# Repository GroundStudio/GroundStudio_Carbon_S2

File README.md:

GroundStudio Carbon S2
====================================

Get it from [ardushop.ro](https://ardushop.ro/en/groundstudio/1814-placa-de-dezvoltare-carbon-s2-6427854000415.html#product-comments-list-header)

Explore all the GroundStudio products at [ardushop.ro](https://ardushop.ro/en/37-groundstudio)

Description
-------------------
Features highly integrated ESP32-S2 with 2.4 GHz WiFi, 4MB Flash, 320kB SRAM, 128kB ROM, 18 GPIO, 10 ADC, 8 touch sensitive pins, 2 UART, I²C 3V3 adapter, RGB smart LED and 1 cell LiPo/LiIon battery charger with optional battery connector.

Contents
-------------------

* [/Documentation](https://github.com/GroundStudio/GroundStudio_Carbon_S2/tree/main/Documentation) -- Pinout.
* [/Hardware](https://github.com/GroundStudio/GroundStudio_Carbon_S2/tree/main/Hardware) -- Schematics, layout.

Versions
-------------------
*(Not all tags shown)*

* [REV0.0.2]
  * changed GPIO3 with GPIO12 between R3 and R8 because GPIO12 cannot be pulled high while in flash mode
  * added 100nF in parallel with R7 for better battery voltage level reading
  * modified the i2c connector label for better visibility
  * adjusted the position of the solder-jumper labels
  * increased the copper fill area under the uC for better cooling

License
-------------------

This is released under the [Attribution-ShareAlike 4.0 International (CC BY-SA 4.0)](https://creativecommons.org/licenses/by-sa/4.0/) license. 
**You are welcome to use this for commercial purposes.**

Please consider contributing back to this project or others to help the open-source hardware community continue to thrive and grow! 

Certifications:

[Open Source Hardware Association](https://certification.oshwa.org/ro000008.html)   
   
[
](https://certification.oshwa.org/ro000008.html)

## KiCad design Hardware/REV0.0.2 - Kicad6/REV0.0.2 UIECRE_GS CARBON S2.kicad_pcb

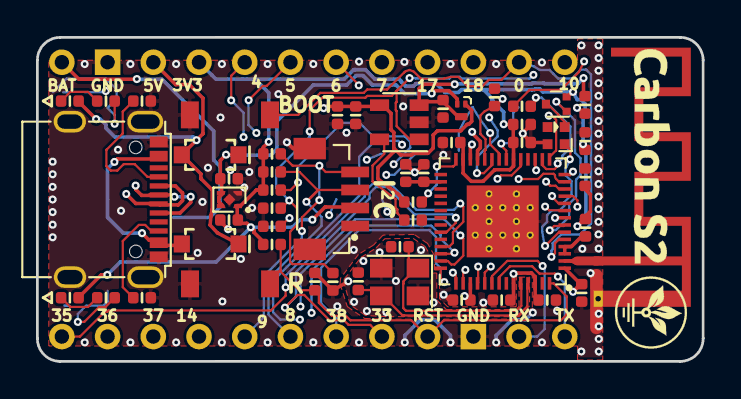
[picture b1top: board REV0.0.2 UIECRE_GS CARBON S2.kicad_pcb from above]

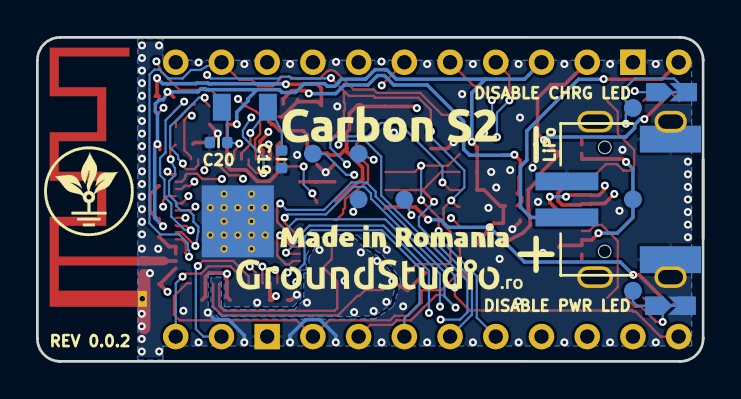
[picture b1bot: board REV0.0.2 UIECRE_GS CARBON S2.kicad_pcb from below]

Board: 4 copper layers, 37.0 x 18.0 mm, 67 parts (8 on the bottom side), 52 nets.

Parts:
A1: SWRA117D_2.4GHz; Texas_SWRA117D_2.4GHz_Left
C1, C4, C8, C9, C11, C14, C15: C_0402_1uF_10V; C_0402_alt
C2: C_0402_100pF_50V; C_0402_alt
C3, C7, C12, C13, C17, C18, C21: C_0402_100nF_16V; C_0402_alt
C5, C6: C_0402_12pF_50V; C_0402_alt
C10, C16: C_0402_10uF_10V; C_0402_alt
C19, C20: DNP C_0402_alt; C_0402_alt
CR1: SOD-123 B0520LW; SOD-123
D1: SOD-123 B0520LW; SOD-123
D2: LED_0402_GREEN; LED_0402_alt
IC1: SOT23-5 BRCL4054CME; SOT-23-5
J1: PWR LED DISABLE; SolderJumper_NC
J2: CHARGING LED DISABLE; SolderJumper_NC
J3, J4: PinHeader_1x12_P2.54_V_M A2541WV-12P; PinHeader_1x12_P2.54mm_Vertical_Male
L1: L_0402_2nH_900mA; L_0402_alt
LED1: SK6805-EC15 DY-S1515065; SK6805-EC15
LED2: LED_0402_RED; LED_0402_alt
Q1: SOT-883 LP0404N3T5G; SOT-883
R1, R12, R13, R16: R_0402_3.3k; R_0402_alt
R2: R_0402_442k; R_0402_alt
R3: R_0402_820k; R_0402_alt
R4, R5: R_0402_5.1k; R_0402_alt
R6, R8: R_0402_2k; R_0402_alt
R7: R_0402_160k; R_0402_alt
R9, R10: R_0402_20k; R_0402_alt
R11, R15: R_0402_100k; R_0402_alt
R14: R_0402_10k; R_0402_alt
REG1: FBP1-1-4_ME6211C33U4AG-N; FBP1-1-4
SW1, SW2: TS342A2P-WZ
T1: SOT-723 DTA143ZMT2L; SOT-723
TP1: TP_USB_VCC; TestPoint
TP2: TP_ONL; TestPoint
TP3: TP_CRGL; TestPoint
TP4: MTCK; TestPoint
TP5: MTDO; TestPoint
TP6: MTDI; TestPoint
TP7: MTMS; TestPoint
U1: QFN-56-1EP_7x7mm ESP32-S2FN4R2; QFN-56-1EP_7x7mm_P0.4mm_EP4x4mm
USB1: USB_C 918-418K2023S40001; USB_C_C167321
X1: SH__1x04_Vertical C145961; SH__1x04_P1.00mm_Vertical
X2: PH__1x02_P2.00mm_Horizontal C47647; PH__1x02_P2.00mm_Horizontal
Y1: Crystal_SMD_3225-4P JF4040M; Crystal_SMD_3225-4Pin_3.2x2.5mm
Y2: DNP Crystal_32.768kHz_SMD; Crystal_32.768kHz_SMD

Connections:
+3V3: C1.1, C2.2, C3.1, C7.1, C9.1, C10.1, C11.1, C12.1, C17.1, C18.1, J4.4, L1.1, LED2.2, R3.1, R12.2, R13.1, R14.2, REG1.1, T1.2, U1.1, U1.20, U1.27, U1.45, U1.51, U1.54, X1.2
+5V: C8.2, CR1.1, Q1.2, REG1.3, REG1.4
+BAT: C16.1, IC1.3, J4.1, Q1.3, R2.2, X2.2
DAC_1: J4.9, U1.23
DAC_2: J4.10, R11.2, U1.24
Feed: A1.1, U1.2
GND: A1.2, C1.2, C2.1, C3.2, C4.2, C5.2, C6.1, C7.2, C8.1, C9.2, C10.2, C11.2, C12.2, C13.2, C14.2, C15.2, C16.2, C17.2, C18.2, C19.2, C20.2, C21.2, IC1.2, J1.2, J3.10, J4.2, LED1.4, R4.2, R5.2, R6.1, R7.1, R11.1, R15.1, R16.1, REG1.2, REG1.5, SW1.1, SW2.1, U1.57, USB1.0, USB1.A1, USB1.A12, USB1.B1, USB1.B12, X1.0, X1.1, X2.0, X2.1, Y1.2, Y1.4
GPIO0: J4.11, SW1.2, U1.5
GPIO1: LED1.1, U1.6
GPIO2: T1.1, U1.7
GPIO3: C21.1, IC1.1, J2.1, R2.1, R7.2, U1.8
GPIO4: J4.5, U1.9
GPIO5: J4.6, U1.10
GPIO6: J4.7, U1.11
GPIO7: J4.8, U1.12
GPIO8: J3.6, R12.1, U1.13, X1.3
GPIO9: J3.5, R13.2, U1.14, X1.4
GPIO10: J4.12, U1.15
GPIO11: R8.2, U1.16
GPIO12: R3.2, R8.1, U1.17
GPIO14: J3.4, U1.19
GPIO21: R1.1, R6.2, U1.28
GPIO33: J3.8, U1.37
GPIO35: J3.1, U1.39
GPIO36: J3.2, U1.40
GPIO37: J3.3, U1.41
GPIO38: J3.7, U1.42
MTCK: TP4.~, U1.43
MTDI: TP6.~, U1.46
MTDO: TP5.~, U1.44
MTMS: TP7.~, U1.47
unnamed: D2.1, R10.1
unnamed: IC1.5, R16.2
unnamed: J1.1, R9.2, TP2.~
unnamed: J2.2, R10.2, TP3.~
unnamed: L1.2, U1.3, U1.4
unnamed: LED1.2, T1.3
unnamed: LED2.1, R9.1
unnamed: R4.1, USB1.B5
unnamed: R5.1, USB1.A5
RESET: C4.1, J3.9, R14.1, SW2.2, U1.56
U0RXD: J3.12, U1.49
U0TXD: J3.11, U1.48
UD+: U1.26, USB1.A6, USB1.B6
UD-: U1.25, USB1.A7, USB1.B7
USB_VCC: C15.1, CR1.2, D1.1, D2.2, IC1.4, J4.3, Q1.1, R1.2, R15.2
VBUS: D1.2, TP1.~, USB1.A4, USB1.A9, USB1.B4, USB1.B9
VDD_SPI: C13.1, C14.1, U1.30
XTAL_32K_N: C19.1, U1.22, Y2.1
XTAL_32K_P: C20.1, U1.21, Y2.2
XTAL_N: C6.2, U1.52, Y1.1
XTAL_P: C5.1, U1.53, Y1.3

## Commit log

2022-08-26 - initial commit
2022-08-26 - added schematic pdf file
2023-03-15 Update README.md
    - removed references to "library"
2023-10-26 - added .step 3D file of the board
2023-11-03 - added datasheet
2023-12-07 - updated pinout and datasheet
2024-07-08 - added 2 arduino code examples
2024-07-08 - updated pinout and datasheet (SPI pins)
